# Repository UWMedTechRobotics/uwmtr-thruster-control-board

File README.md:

# Thruster Control Board - Revision 2

## Progress Notes
- Designed circuit board revision 1 using Altium Designer.
- Wrote firmware for testing circuitry on revision 1.
    - Wasn't able to use revision 1 tests due to faults in circuit design.
- Designed circuit board revision 2 using Altium Designer.

## Todo Things & Priority
### High
- [x] [@AdrianTarantino](https://github.com/AdrianTarantino) | Solder crystal 
oscillator to board.

- [ ] Test device functionality. View [this repository](https://github.com/UWMedTechRobotics/ESC_V1_Firmware_Tests/tree/main).
    - [ ] Validate I2C, GPIO, PWM and ADC.

- [ ] Implement firmware for interfacing with onboard electronics:
    - [ ] [IMU (BNO055)](https://www.bosch-sensortec.com/media/boschsensortec/downloads/datasheets/bst-bno055-ds000.pdf).
    Note that this may be controlled by Orange Pi instead.
    - [ ] Leak Sensor (ask Daniel).
    - [ ] Solonoids (ask Daniel).
    - [ ] Serial communication via USB Type-C.
        - Speak with Abdur about what information needs to be communicated and
        how that information needs to be formatted.
        - Use PuTTY to validate that it's working.
    - [ ] [@AdrianTarantino](https://github.com/AdrianTarantino) | 3-Phase BLDC 
    motors.
    - [x] [@AdrianTarantino](https://github.com/AdrianTarantino) | Muxes
    - [x] [@AdrianTarantino](https://github.com/AdrianTarantino) | [LED Driver](https://use.365.altium.com/librarycomponentsapi/api/v1/References/6CBF2630-7D49-4BC0-9B47-311861A12B9A). LED colour should follow this
    priority:
        - Red when failure.
        - Green when motors spinning.
        - Purple when communicating with external device.
        - Blue when idle.

### Medium
- [ ] Conan | Design mounting bracket for board.

- [ ] Source stantions for stacking power board, sonar board and thruster board.

### Low
- [ ] Develop diagnostic app:
    - Desktop app on PC
    - Sends commands via USB to the board.

- [ ] Add release to [GitHub repository](https://github.com/UWMedTechRobotics/uwmtr-thruster-control-board).
    - STEP file.
    - NC Drill, Gerber
    - BOM, Pick & Place

- [ ] Document everything that needs to be changed for revision 3:
    - [ ] Add 3-phase BLDC driver chip.
        - Ideally be able to set speed & direction via I2C or SPI.
    - [ ] Add BNO055 IMU to the board instead of the current IMU on the board.
    - [ ] Replace the debug connector with pin headers.
    - [ ] Add USB to UART chip to simplify USB communications.
    - [ ] Add an additional onboard LED purely for signalling that power is on.
     
## Issues
### I2C SDA high voltage is 0.50V and idle voltage is 0.50V.
- Slave device could be tying the line down (LP5817DRLR).
- Low resistance between SDA and ground could be creating a voltage divider.
- High resistance between SDA and +3.3V could be creating a voltage drop.
- Check if other boards have this same issue.

# Revision 3 Notes
## Electrical
- Update motor control circuitry to use [the TI MCF8316A](https://www.ti.com/product/MCF8316A#pps).
    - Significantly simplifies electrical system and number of components on the board.
    - Available on JLCPCB parts library.
- Simplify USB communication with [TI TUSB3410](https://www.ti.com/product/TUSB3410).
    - Converts USB data to UART.
 - Add [BNO055](https://www.digikey.ca/short/m2jcv0r0) for IMU related data.
    - Available on JLCPCB parts library.
- Add dedicated LED purely for indicating power-on.
- Use Power MOSFETs

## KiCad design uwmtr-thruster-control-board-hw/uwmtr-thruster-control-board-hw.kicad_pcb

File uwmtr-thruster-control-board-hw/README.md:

# Notes
- Voltage for buck converter must be set with `BUCK_SEL` parameters
    
    | `BUCK_SEL` Value | Voltage |
    | ---------------- | ------- |
    | 0b00 | 3.1 < 3.3 < 3.5 |
    | 0b01 | 4.6 < 5.0 < 5.4 |
    | 0b10 | 3.7 < 4.0 < 4.3 |
    | 0b11 | 5.2 < 5.7 < 6.2 | 

- Source THT 22R 1W resistor for buck converter with.

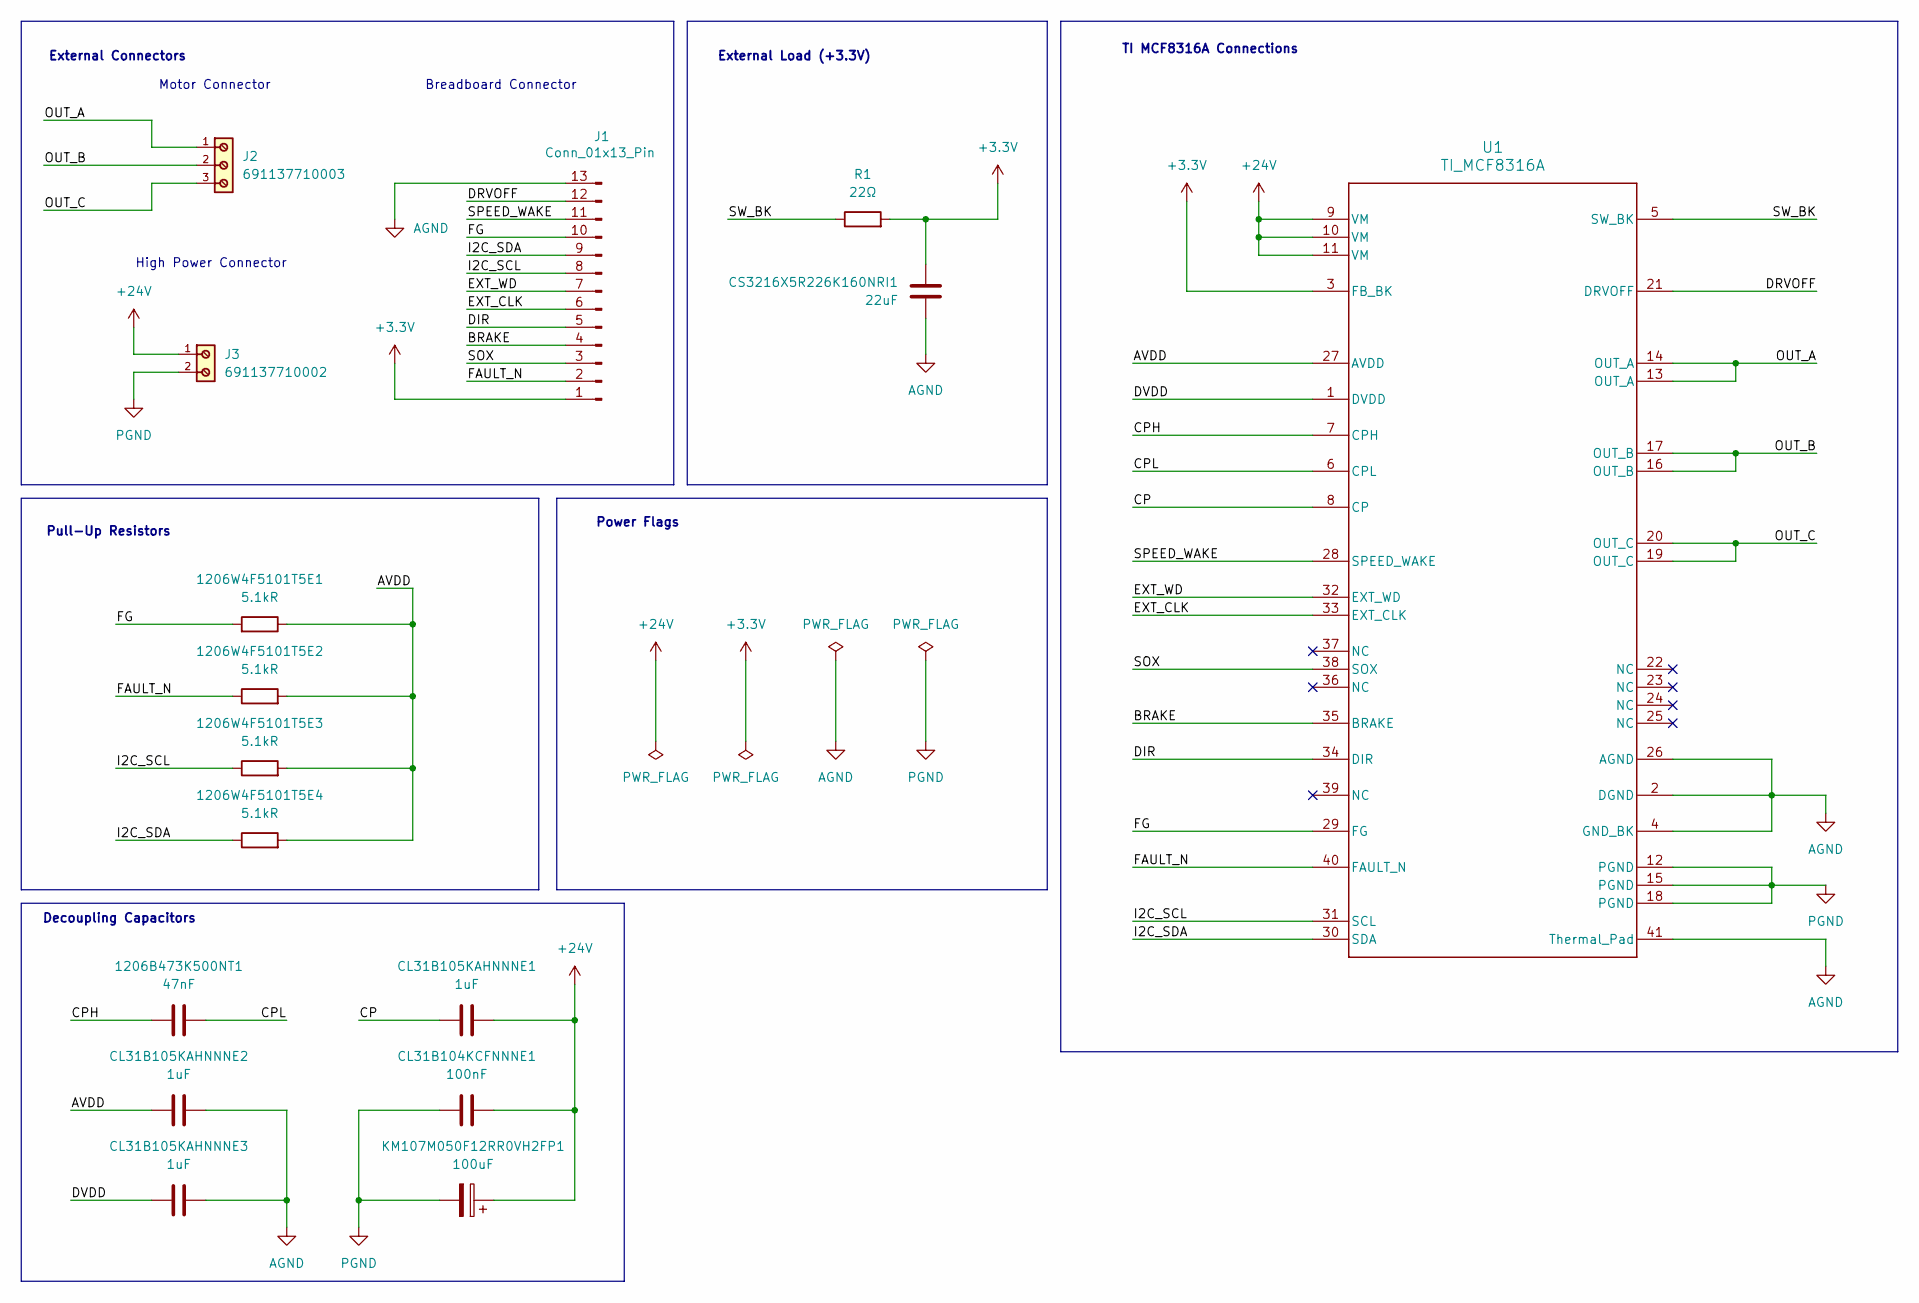
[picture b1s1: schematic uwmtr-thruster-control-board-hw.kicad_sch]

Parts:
1206B473K500NT1: 47nF; C_1206_3216Metric; JLCPCB Part # C1870
1206W4F5101T5E1, 1206W4F5101T5E2, 1206W4F5101T5E3, 1206W4F5101T5E4: 5.1kR; R_1206_3216Metric; JLCPCB Part # C26033
CL31B104KCFNNNE1: 100nF; C_1206_3216Metric; JLCPCB Part # C1945
CL31B105KAHNNNE1, CL31B105KAHNNNE2, CL31B105KAHNNNE3: 1uF; C_1206_3216Metric; JLCPCB Part # C28322
CS3216X5R226K160NRI1: 22uF; C_1206_3216Metric; JLCPCB Part # C513771
J1: Conn_01x13_Pin; PinSocket_1x13_P2.54mm_Vertical
J2: 691137710003
J3: 691137710002
KM107M050F12RR0VH2FP1: 100uF; C_Radial_D8.0mm_H11.5mm_P3.50mm; JLCPCB Part # C2749
R1: 22Ω; R_Axial_DIN0207_L6.3mm_D2.5mm_P10.16mm_Horizontal
U1: TI_MCF8316A; JLCPCB Part # C3681167

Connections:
+3.3V: CS3216X5R226K160NRI1.1, J1.1 (Pin_13), R1.2, U1.3 (FB_BK)
+24V: CL31B104KCFNNNE1.2, CL31B105KAHNNNE1.1, J3.1, KM107M050F12RR0VH2FP1.1, U1.9 (VM), U1.10 (VM), U1.11 (VM)
/AVDD: 1206W4F5101T5E1.1, 1206W4F5101T5E2.2, 1206W4F5101T5E3.2, 1206W4F5101T5E4.2, CL31B105KAHNNNE2.2, U1.27 (AVDD)
/BRAKE: J1.4 (Pin_10), U1.35 (BRAKE)
/CP: CL31B105KAHNNNE1.2, U1.8 (CP)
/CPH: 1206B473K500NT1.1, U1.7 (CPH)
/CPL: 1206B473K500NT1.2, U1.6 (CPL)
/DIR: J1.5 (Pin_9), U1.34 (DIR)
/DRVOFF: J1.12 (Pin_2), U1.21 (DRVOFF)
/DVDD: CL31B105KAHNNNE3.2, U1.1 (DVDD)
/EXT_CLK: J1.6 (Pin_8), U1.33 (EXT_CLK)
/EXT_WD: J1.7, U1.32 (EXT_WD)
/FAULT_N: 1206W4F5101T5E2.1, J1.2 (Pin_12), U1.40 (FAULT_N)
/FG: 1206W4F5101T5E1.2, J1.10 (Pin_4), U1.29 (FG)
/I2C_SCL: 1206W4F5101T5E3.1, J1.8 (Pin_6), U1.31 (SCL)
/I2C_SDA: 1206W4F5101T5E4.1, J1.9 (Pin_5), U1.30 (SDA)
/OUT_A: J2.1, U1.13 (OUT_A), U1.14 (OUT_A)
/OUT_B: J2.2, U1.16 (OUT_B), U1.17 (OUT_B)
/OUT_C: J2.3, U1.19 (OUT_C), U1.20 (OUT_C)
/SOX: J1.3 (Pin_11), U1.38 (SOX)
/SPEED_WAKE: J1.11 (Pin_3), U1.28 (SPEED_WAKE)
/SW_BK: R1.1, U1.5 (SW_BK)
AGND: CL31B105KAHNNNE2.1, CL31B105KAHNNNE3.1, CS3216X5R226K160NRI1.2, J1.13 (Pin_1), U1.2 (DGND), U1.4 (GND_BK), U1.26 (AGND), U1.41 (Thermal_Pad)
PGND: CL31B104KCFNNNE1.1, J3.2, KM107M050F12RR0VH2FP1.2, U1.12 (PGND), U1.15 (PGND), U1.18 (PGND)

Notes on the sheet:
High Power Connector
Decoupling Capacitors
External Connectors
Power Flags
Pull-Up Resistors
TI MCF8316A Connections
Motor Connector
Breadboard Connector
External Load (+3.3V)

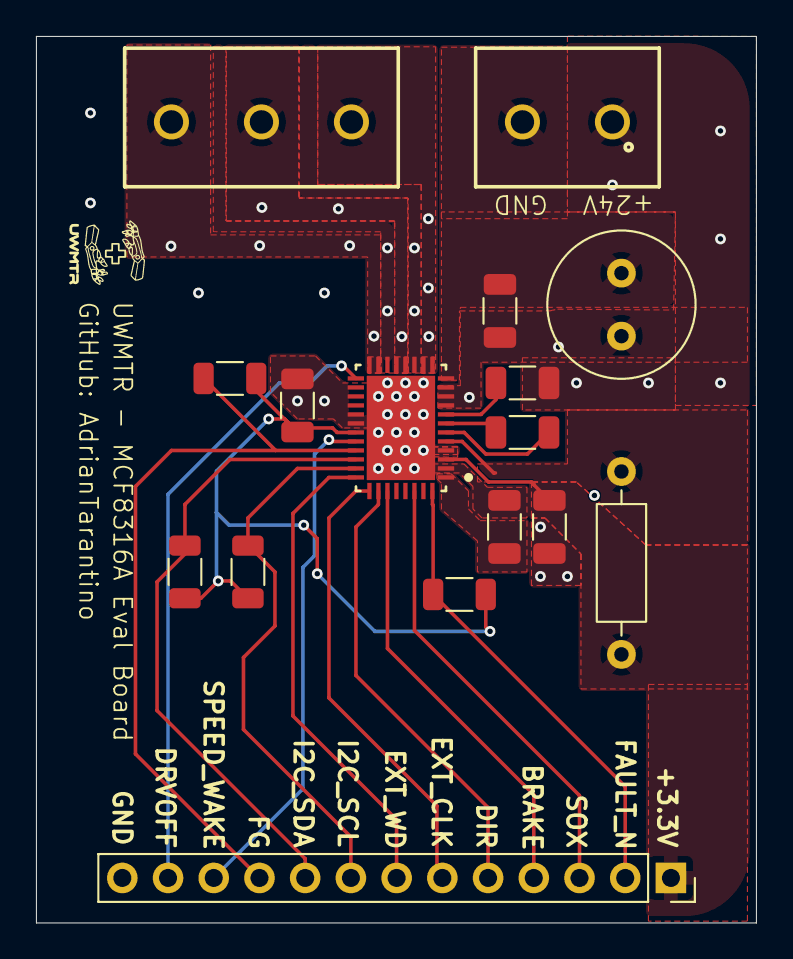
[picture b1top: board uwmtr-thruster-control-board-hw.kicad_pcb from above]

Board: 4 copper layers, 40.0 x 49.2 mm, 16 parts (0 on the bottom side), 24 nets.
